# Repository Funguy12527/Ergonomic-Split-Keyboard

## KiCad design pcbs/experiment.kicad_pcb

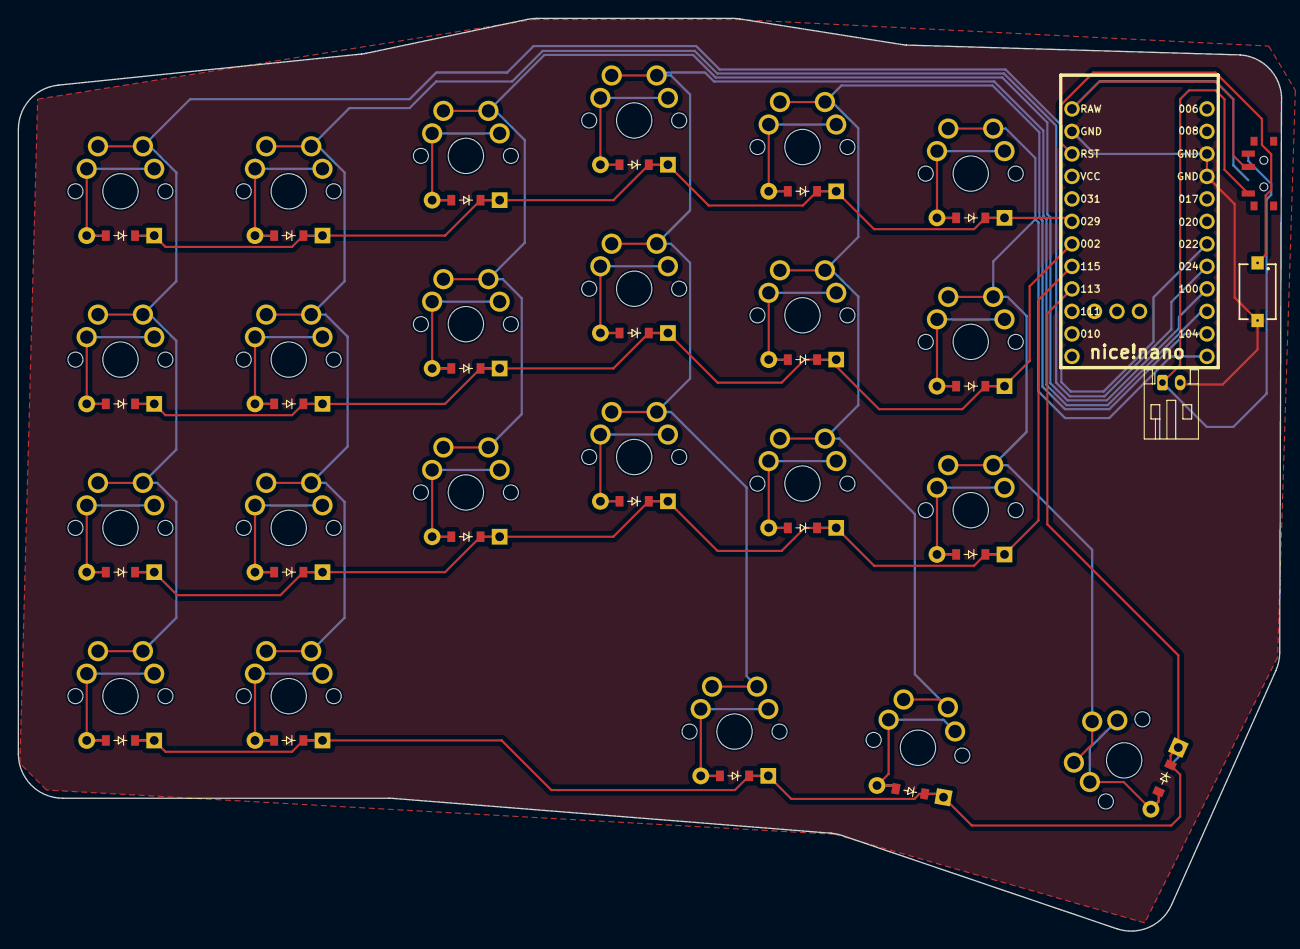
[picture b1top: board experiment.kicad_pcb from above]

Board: 2 copper layers, 142.6 x 103.1 mm, 50 parts (0 on the bottom side), 37 nets.

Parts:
D1, D2, D3, D4, D5, D6, D7, D8, D9, D10, D11, D12, D13, D14, D15, D16, D17, D18, D19, D20, D21, D22, D23: ComboDiode
MCU1: nice_nano
S1, S2, S3, S4, S5, S6, S7, S8, S9, S10, S11, S12, S13, S14, S15, S16, S17, S18, S19, S20, S21, S22, S23: MX
S24: 434121025816
T1: SW_SPDT_PCM12
_1: JST_PH_S2B-PH-K_1x02_P2.00mm_Horizontal

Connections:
GND: MCU1.3, MCU1.4, MCU1.23, S24.2, _1.2
P002: D3.1, D7.1, D10.1, D13.1, D16.1, D19.1, MCU1.18
P011: MCU1.10, S12.1, S13.1, S14.1, S21.1
P022: MCU1.7, S1.1, S2.1, S3.1, S4.1
P024: MCU1.8, S5.1, S6.1, S7.1, S8.1
P029: D4.1, D8.1, D11.1, D14.1, D17.1, D20.1, MCU1.19
P100: MCU1.9, S9.1, S10.1, S11.1
P104: MCU1.11, S15.1, S16.1, S17.1, S22.1
P106: MCU1.12, S18.1, S19.1, S20.1, S23.1
P113: D1.1, D5.1, D21.1, D22.1, D23.1, MCU1.16
P115: D2.1, D6.1, D9.1, D12.1, D15.1, D18.1, MCU1.17
RAW: MCU1.24, T1.2
RST: MCU1.22, S24.1
index_home: D16.2, S16.2
index_low: D15.2, S15.2
index_top: D17.2, S17.2
indexfar_home: D19.2, S19.2
indexfar_low: D18.2, S18.2
indexfar_top: D20.2, S20.2
layer1_layerkey: D22.2, S22.2
layer2_layerkey: D21.2, S21.2
middle_home: D13.2, S13.2
middle_low: D12.2, S12.2
middle_top: D14.2, S14.2
pinky_home: D7.2, S7.2
pinky_low: D6.2, S6.2
pinky_mod: D5.2, S5.2
pinky_top: D8.2, S8.2
pinkyfar_home: D3.2, S3.2
pinkyfar_low: D2.2, S2.2
pinkyfar_mod: D1.2, S1.2
pinkyfar_top: D4.2, S4.2
pos: T1.1, _1.1
ring_home: D10.2, S10.2
ring_low: D9.2, S9.2
ring_top: D11.2, S11.2
space_layerkey: D23.2, S23.2

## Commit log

2025-10-31 Full Project Commit
2025-11-01 PCB commit
